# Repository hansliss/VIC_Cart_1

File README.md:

# VIC_Cart_1
A basic programmable RAM/ROM expansion for VIC-20

RAM is handled by an KM681000CLG-5L, 128kx8 static RAM
~RAM1,~RAM2,~RAM3 are NAND:ed together, so the 3k area is handled as a single block
A0-A13 are provided by the cartridge port, while A14 and A15 are connected to ~BLK2 and ~BLK1, respectively.
With 8k blocks (using 13 address lines)

NOTE: The RAM addressing is incorrect and needs to be fixed!

blk	addresses	
0	0400-0fff       01111  01
1	2000-3fff	10111  11
2	4000-5fff	11011  00
3	6000-7fff	11101  01
5	a000-bfff	11110  11

U4C: 3-input AND
U5D: 2-input OR

BLK0 OR BLK2 OR BLK3 = A13
BLK2 = A14

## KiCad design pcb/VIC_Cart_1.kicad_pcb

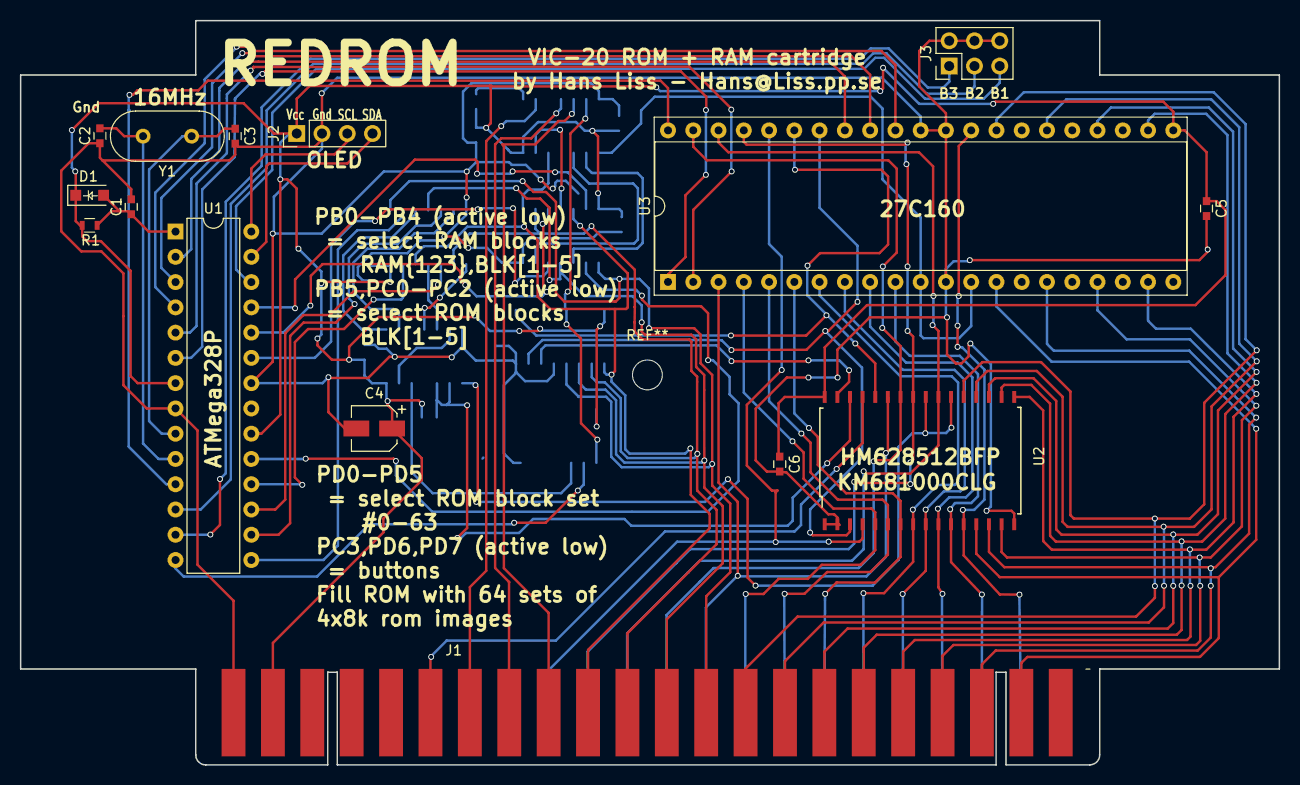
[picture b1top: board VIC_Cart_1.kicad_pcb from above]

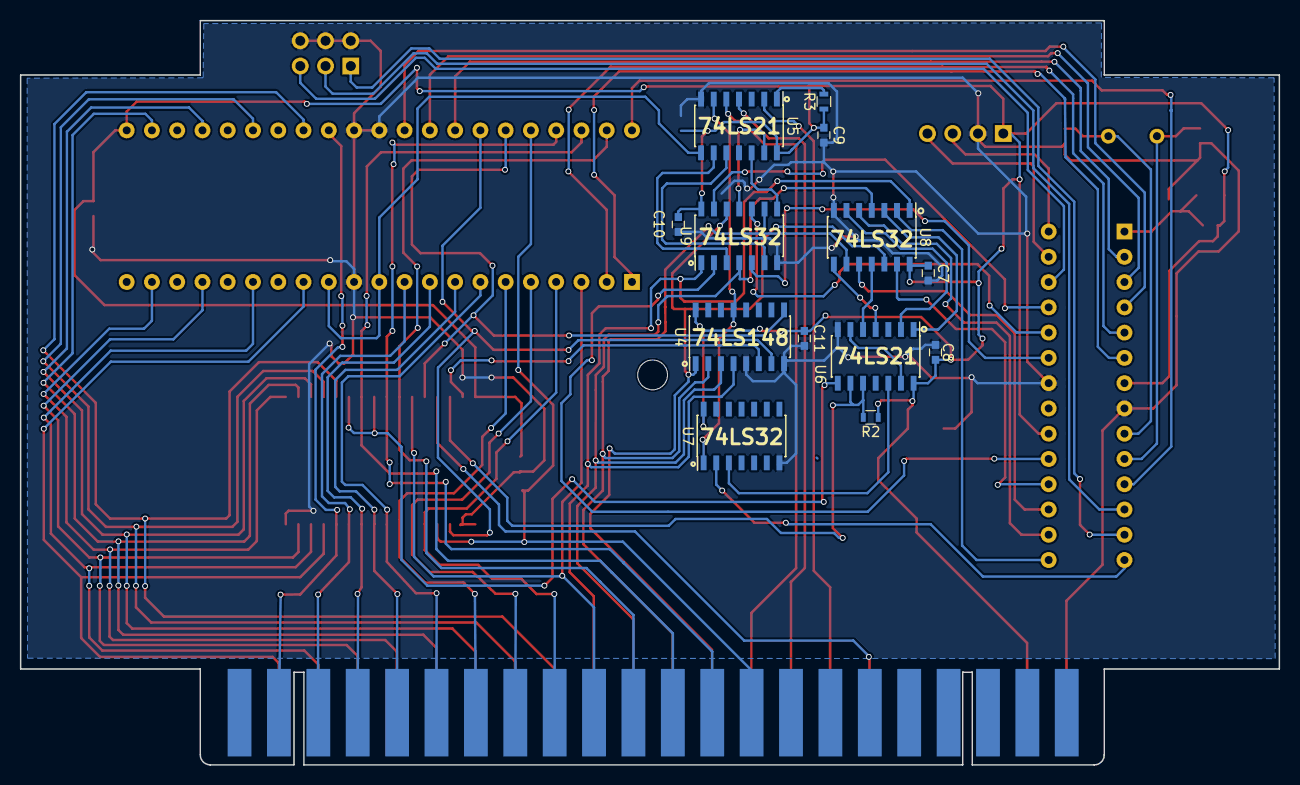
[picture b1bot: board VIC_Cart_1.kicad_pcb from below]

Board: 2 copper layers, 126.5 x 74.8 mm, 28 parts (13 on the bottom side), 72 nets.

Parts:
C1: 100nf; C_0603
C2, C3: 22pf; C_0603
C4: 10uf; CP_Elec_4x5.8
C5, C6, C7, C8, C9, C10, C11: 0.1uf; C_0603
D1: 1N4148; D_SOD-123F
J1: VIC-20_Expansion_Port; VIC_EXP
J2: I2C Display; Pin_Header_Straight_1x04_Pitch2.54mm
J3: Buttons; Pin_Header_Straight_2x03_Pitch2.54mm
R1, R2, R3: 10k; R_0603
U1: ATMEGA328P-PU; DIP-28_W7.62mm
U2: HM628512BFP-5; SOP-32_14.12x20.87mm_Pitch1.27mm
U3: M27C160; DIP-42_W15.24mm_Socket
U4: 74LS148; SOIC-16_3.9x9.9mm_Pitch1.27mm
U5, U6: 74LS21; SOIC-14_3.9x8.7mm_Pitch1.27mm
U7, U8, U9: 74LS32; SOIC-14_3.9x8.7mm_Pitch1.27mm
Y1: 16MHz; Crystal_HC49-4H_Vertical

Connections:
/OLED_SCL: J2.3, U1.28
/OLED_SDA: J2.4, U1.27
/V_RW: J1.17, U2.29
/~BLK1: J1.10, U4.4, U8.1, U9.1
/~BLK2: J1.11, U4.3, U8.4, U9.4
/~BLK3: J1.12, U4.2, U8.9, U9.9
/~BLK5: J1.13, U4.1, U8.12, U9.12
/~BUTTON1: J3.5, U1.26
/~BUTTON2: J3.3, U1.12
/~BUTTON3: J3.1, U1.13
/~RAM: U4.13, U5.6, U7.1
/~RESET: C1.1, D1.2, R1.2, U1.1
/~SEL_RAM_3k: U1.14, U7.2
/~SEL_RAM_BLK1: U1.15, U8.2
/~SEL_RAM_BLK2: U1.16, U8.5
/~SEL_RAM_BLK3: U1.17, U8.10
/~SEL_RAM_BLK5: U1.18, U8.13
/~SEL_ROM_BLK1: U1.19, U9.2
/~SEL_ROM_BLK2: U1.23, U9.5
/~SEL_ROM_BLK3: U1.24, U9.10
/~SEL_ROM_BLK5: U1.25, U9.13
A0: J1.B, U2.12, U3.30
A1: J1.C, U2.11, U3.10
A2: J1.D, U2.10, U3.9
A3: J1.E, U2.9, U3.8
A4: J1.F, U2.8, U3.7
A5: J1.H, U2.7, U3.6
A6: J1.J, U2.6, U3.5
A7: J1.K, U2.5, U3.4
A8: J1.L, U2.27, U3.3
A9: J1.M, U2.26, U3.41
A10: J1.N, U2.23, U3.40
A11: J1.P, U2.25, U3.39
A12: J1.R, U2.4, U3.38
BA0: U2.28, U3.37, U4.9
BA1: U2.3, U3.36, U4.7
BA2: U2.31, U4.6
D0: J1.2, U2.13, U3.14
D1: J1.3, U2.14, U3.16
D2: J1.4, U2.15, U3.18
D3: J1.5, U2.17, U3.20
D4: J1.6, U2.18, U3.23
D5: J1.7, U2.19, U3.25
D6: J1.8, U2.20, U3.27
D7: J1.9, U2.21, U3.29
GND: C1.2, C2.1, C3.2, C4.2, C5.2, C6.2, C7.2, C8.2, C9.2, C10.2, C11.2, J1.22, J2.2, J3.2, J3.4, J3.6, U1.8, U1.22, U2.1, U2.2, U2.16, U3.12, U3.31, U3.32, U4.5, U4.8, U5.7, U6.7, U7.7, U8.7, U9.7
unnamed: C2.2, U1.10, Y1.2
unnamed: C3.1, U1.9, Y1.1
unnamed: J1.14, U5.5
unnamed: J1.15, U5.4
unnamed: J1.16, U5.2
unnamed: R2.2, U2.30, U6.9, U6.10
unnamed: R3.2, U5.1
unnamed: U2.22, U2.24, U6.8
unnamed: U3.11, U3.13, U5.8
unnamed: U5.9, U9.3
unnamed: U5.10, U9.6
unnamed: U5.12, U9.8
unnamed: U5.13, U9.11
unnamed: U6.1, U8.3
unnamed: U6.2, U8.6
unnamed: U6.4, U8.8
unnamed: U6.5, U8.11
unnamed: U6.12, U7.3
unnamed: U6.6, U6.13
RB0: U1.2, U3.35
RB1: U1.3, U3.34
RB2: U1.4, U3.33
RB3: U1.5, U3.2
RB4: U1.6, U3.1
RB5: U1.11, U3.42
VCC: C4.1, C5.1, C6.1, C7.1, C8.1, C9.1, C10.1, C11.1, D1.1, J1.21, J2.1, R1.1, R2.1, R3.1, U1.7, U1.20, U2.32, U3.22, U4.16, U5.14, U6.14, U7.14, U8.14, U9.14

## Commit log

2018-07-10 Initial import
2018-07-11 Added A13/A14 to RAM for correct block addressing
2018-07-11 Working on the RAM addressing scheme - currently incorrect
2018-07-11 More work on addressing
2018-07-13 Massive redesign to fix block address encoding from the expansion port signals
2018-07-13 Added Connectors lib Cleaned up libs by removing unused components
2018-07-13 Added Footprint library to project Added explanatory text to PCB
2018-07-14 Added back ground plane
2018-07-14 Switched around BLK[1-5] to encoder to put ROM blocks in correct order.
2018-07-17 Minor change
2018-07-17 Moved PCB files to subdirectory
2018-07-19 Added notes.txt with component list
2018-07-24 Arduino code added
2018-07-25 Better debouncing More compact code Added BLK3+BLK5 as a ROM mode
2018-07-29 Changed pads to pin header footprint for buttons Inverted BLK inputs to encoder to correct addressing error Added component values to silkscreen
2018-07-29 No change
2018-07-31 Added mounting hole Added title
2018-07-31 Moved button pin header to the right Changed outline to match existing (large) carts, e.g. 16k expansion
2018-07-31 Changed silkscreen text
2018-08-03 Moved capacitor to back Grounded A17, A18 for 512k RAM Added RAM chip to project lib
2018-08-06 Create LICENSE
